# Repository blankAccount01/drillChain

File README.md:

# DrillChain
A keychain shaped to look like a big drill that uses a bistable multivibrator circuit to toggle the mini motor disc off and on.

# Schematic

# PCB

# BOM
- 1 Battery holder
- 2 NPN tranistors
- 2 420Ω resistors
- 4 4.2kΩ resistors
- 1 mini motor disc
- 2 push buttons

Made by `@freshlemon` on Slack

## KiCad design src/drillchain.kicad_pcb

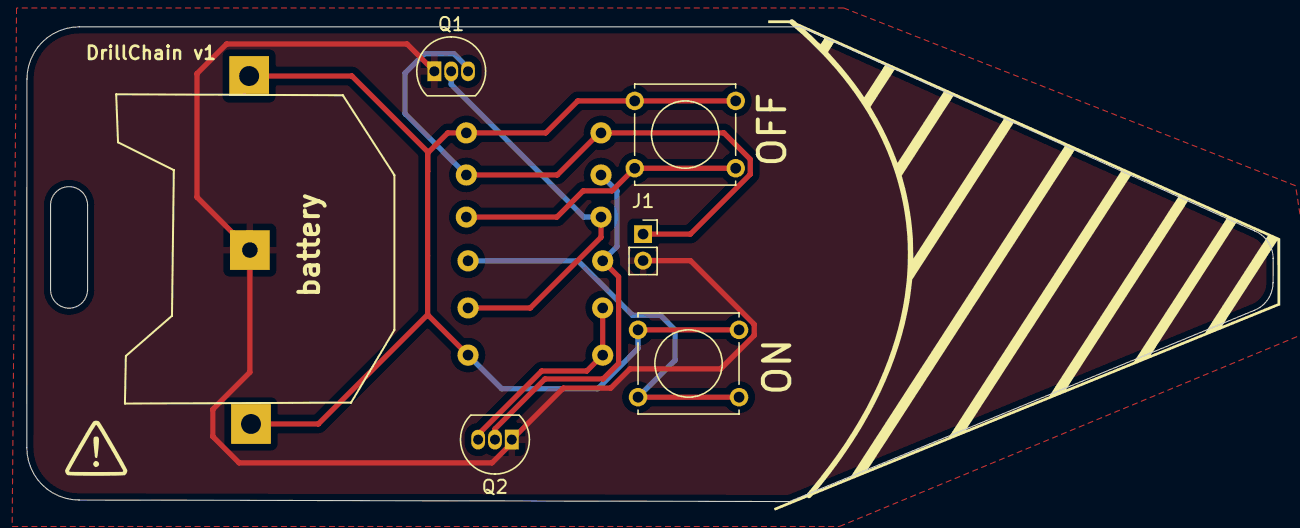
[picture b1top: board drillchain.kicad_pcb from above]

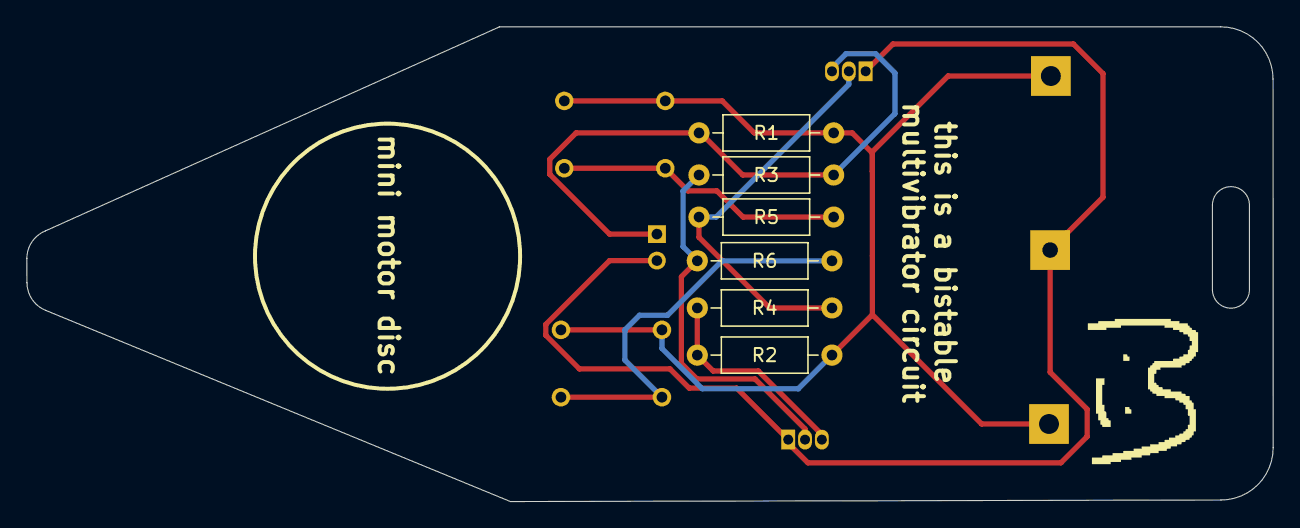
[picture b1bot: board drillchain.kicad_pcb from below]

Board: 2 copper layers, 94.0 x 35.8 mm, 12 parts (6 on the bottom side), 8 nets.

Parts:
BAT1: BS-7; Battery_Holder_Coin_2032_BS-7
J1: Conn_01x02_Socket; PinSocket_1x02_P2.00mm_Vertical
OFF: SW_Push; SW_Tactile_Straight_KSL0Axx1LFTR
ON: SW_Push; SW_Tactile_Straight_KSL0Axx1LFTR
Q1, Q2: 2N3904; TO-92_Inline
R1, R2: 20; R_Axial_DIN0207_L6.3mm_D2.5mm_P10.16mm_Horizontal
R3, R4: 700; R_Axial_DIN0207_L6.3mm_D2.5mm_P10.16mm_Horizontal
R5, R6: 1k; R_Axial_DIN0207_L6.3mm_D2.5mm_P10.16mm_Horizontal

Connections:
+3.3V: BAT1.Pos, OFF.1, ON.1, R1.1, R2.1
GND: BAT1.Neg, J1.2, Q1.1 (E), Q2.1 (E)
unnamed: J1.1, Q1.3 (C), R1.2, R3.1
unnamed: Q1.2 (B), R4.1, R5.2
unnamed: Q2.2 (B), R3.2, R6.2
unnamed: Q2.3 (C), R2.2, R4.2
unnamed: OFF.2, R5.1
unnamed: ON.2, R6.1

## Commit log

2025-05-08 Updated Resistors
